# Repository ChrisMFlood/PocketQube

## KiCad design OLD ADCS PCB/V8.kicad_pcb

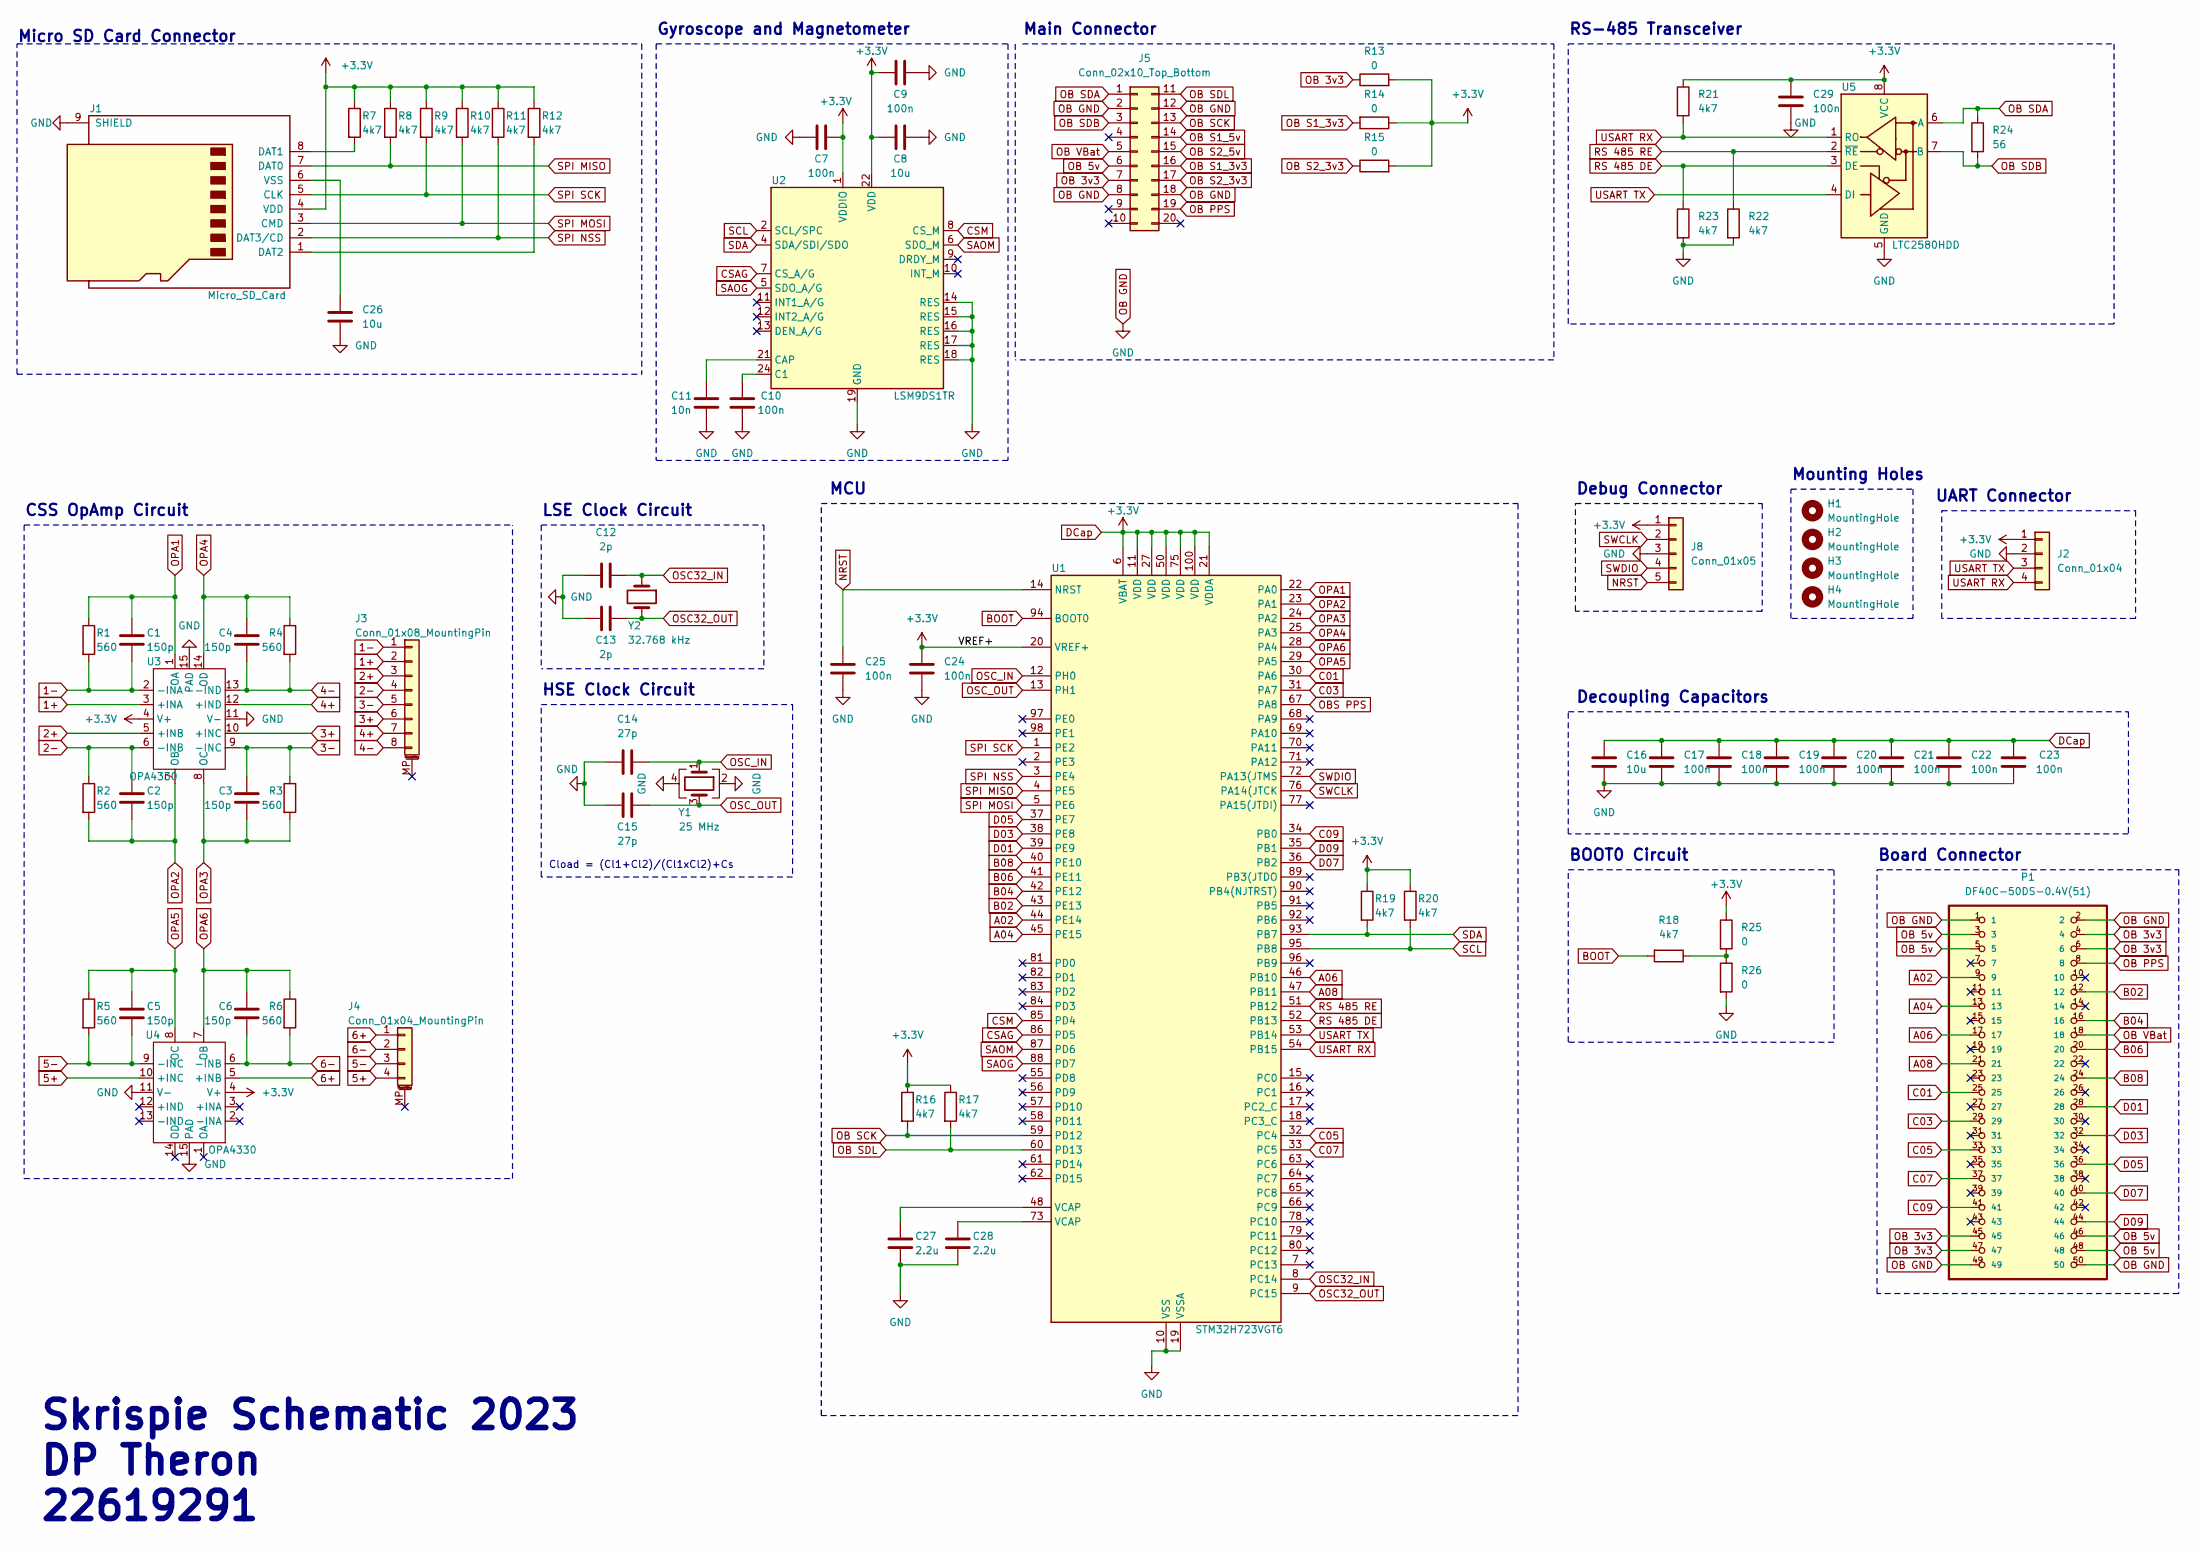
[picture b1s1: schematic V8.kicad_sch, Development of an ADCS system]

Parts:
C1, C2, C3, C4, C5, C6: 150p; C_0201_0603Metric
C7, C9, C10, C17, C18, C19, C20, C21, C22, C23, C24, C25, C29: 100n; C_0201_0603Metric
C8, C16, C26: 10u; C_0201_0603Metric
C11: 10n; C_0201_0603Metric
C12, C13: 2p; C_0201_0603Metric
C14, C15: 27p; C_0201_0603Metric
C27, C28: 2.2u; C_0201_0603Metric
H1, H2, H3, H4: MountingHole; MountingHole_2.5mm
J1: Micro_SD_Card; microSD_HC_Hirose_DM3AT-SF-PEJM5
J2: Conn_01x04; PinHeader_1x04_P1.27mm_Vertical
J3: Conn_01x08_MountingPin; JST_GH_SM08B-GHS-TB_1x08-1MP_P1.25mm_Horizontal
J4: Conn_01x04_MountingPin; JST_GH_SM04B-GHS-TB_1x04-1MP_P1.25mm_Horizontal
J5: Conn_02x10_Top_Bottom; SAMTEC-SMH-110-02-X-D_SMD
J8: Conn_01x05; PinHeader_1x05_P1.27mm_Vertical
P1: DF40C-50DS-0.4V(51); HRS_DF40C-50DS-0.4V(51)
R1, R2, R3, R4, R5, R6: 560; R_0201_0603Metric
R7, R8, R9, R10, R11, R12, R16, R17, R18, R19, R20, R21, R22, R23: 4k7; R_0201_0603Metric
R13, R14, R15, R25, R26: 0; R_0201_0603Metric
R24: 56; R_0201_0603Metric
U1: STM32H723VGT6; LQFP-100_14x14mm_P0.5mm
U2: LSM9DS1TR; LGA-24L_3x3.5mm_P0.43mm
U3, U4: OPA4330; Texas_S-PVQFN-N14
U5: LTC2580HDD; DFN-8-1EP_3x3mm_P0.5mm_EP1.65x2.38mm
Y1: 25 MHz; Crystal_SMD_EuroQuartz_X22-4Pin_2.5x2.0mm
Y2: 32.768 kHz; Crystal_SMD_EuroQuartz_EQ161-2Pin_3.2x1.5mm

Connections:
1+: J3.2, U3.3 (+INA)
1-: C1.2, J3.1, R1.2, U3.2 (-INA)
2+: J3.3, U3.5 (+INB)
2-: C2.1, J3.4, R2.1, U3.6 (-INB)
3+: J3.6, U3.10 (+INC)
3-: C3.1, J3.5, R3.1, U3.9 (-INC)
4+: J3.7, U3.12 (+IND)
4-: C4.2, J3.8, R4.2, U3.13 (-IND)
5+: J4.4, U4.10 (+INC)
5-: C5.2, J4.3, R5.2, U4.9 (-INC)
6+: J4.1, U4.5 (+INB)
6-: C6.2, J4.2, R6.2, U4.6 (-INB)
A02: P1.9, U1.44 (PE14)
A04: P1.13, U1.45 (PE15)
A06: P1.17, U1.46 (PB10)
A08: P1.21, U1.47 (PB11)
B02: P1.12, U1.43 (PE13)
B04: P1.16, U1.42 (PE12)
B06: P1.20, U1.41 (PE11)
B08: P1.24, U1.40 (PE10)
BOOT: R18.2, U1.94 (BOOT0)
C01: P1.25, U1.30 (PA6)
C03: P1.29, U1.31 (PA7)
C05: P1.33, U1.32 (PC4)
C07: P1.37, U1.33 (PC5)
C09: P1.41, U1.34 (PB0)
CSAG: U1.86 (PD5), U2.7 (CS_A/G)
CSM: U1.85 (PD4), U2.8 (CS_M)
D01: P1.28, U1.39 (PE9)
D03: P1.32, U1.38 (PE8)
D05: P1.36, U1.37 (PE7)
D07: P1.40, U1.36 (PB2)
D09: P1.44, U1.35 (PB1)
DCap: C7.2, C8.1, C9.1, C16.1, C17.1, C18.1, C19.1, C20.1, C21.1, C22.1, C23.1, C24.1, C29.1, J1.4 (VDD), J2.1, J8.1, R7.1, R8.1, R9.1, R10.1, R11.1, R12.1, R13.2, R14.1, R15.2, R16.1, R17.1, R19.1, R20.1, R21.1, R25.1, U1.6 (VBAT), U1.11 (VDD), U1.20 (VREF+), U1.21 (VDDA), U1.27 (VDD), U1.50 (VDD), U1.75 (VDD), U1.100 (VDD), U2.1 (VDDIO), U2.3 (VDDIO), U2.22 (VDD), U2.23 (VDD), U3.4 (V+), U4.4 (V+), U5.8 (VCC)
NRST: C25.1, J8.5, U1.14 (NRST)
unnamed: C27.1, U1.48 (VCAP)
unnamed: C28.1, U1.73 (VCAP)
unnamed: J1.8 (DAT1), R7.2
unnamed: J1.1 (DAT2), R12.2
unnamed: C26.1, J1.6 (VSS)
unnamed: R18.1, R25.2, R26.1
unnamed: C10.1, U2.24 (C1)
unnamed: C11.2, U2.21 (CAP)
OB 3v3: J5.7, P1.4, P1.6, P1.45, P1.47, R13.1
OB 5v: J5.6, P1.3, P1.5, P1.46, P1.48
OB GND: C7.1, C8.2, C9.2, C10.2, C11.1, C12.1, C13.1, C14.1, C15.1, C16.2, C17.2, C18.2, C19.2, C20.2, C21.2, C22.2, C23.2, C24.2, C25.2, C26.2, C27.2, C28.2, C29.2, J1.9 (SHIELD), J2.2, J5.2, J5.8, J5.12, J5.18, J8.3, P1.1, P1.2, P1.49, P1.50, R22.2, R23.2, R26.2, U1.10 (VSS), U1.19 (VSSA), U1.26 (VSS), U1.49 (VSS), U1.74 (VSS), U1.99 (VSS), U2.14 (RES), U2.15 (RES), U2.16 (RES), U2.17 (RES), U2.18 (RES), U2.19 (GND), U2.20 (GND), U3.11 (V-), U3.15 (PAD), U4.11 (V-), U4.15 (PAD), U5.5 (GND), U5.9 (GND), Y1.2, Y1.4
OB PPS: J5.19, P1.8
OB S1_3v3: J5.16, R14.2
OB S1_5v: J5.14
OB S2_3v3: J5.17, R15.1
OB S2_5v: J5.15
OB SCK: J5.13, R16.2, U1.59 (PD12)
OB SDA: J5.1, R24.1, U5.6 (A)
OB SDB: J5.3, R24.2, U5.7 (B)
OB SDL: J5.11, R17.2, U1.60 (PD13)
OB VBat: J5.5, P1.18
OBS PPS: U1.67 (PA8)
OPA1: C1.1, R1.1, U1.22 (PA0), U3.1 (OA)
OPA2: C2.2, R2.2, U1.23 (PA1), U3.7 (OB)
OPA3: C3.2, R3.2, U1.24 (PA2), U3.8 (OC)
OPA4: C4.1, R4.1, U1.25 (PA3), U3.14 (OD)
OPA5: C5.1, R5.1, U1.29 (PA5), U4.8 (OC)
OPA6: C6.1, R6.1, U1.28 (PA4), U4.7 (OB)
OSC32_IN: C12.2, U1.8 (PC14), Y2.1
OSC32_OUT: C13.2, U1.9 (PC15), Y2.2
OSC_IN: C14.2, U1.12 (PH0), Y1.1
OSC_OUT: C15.2, U1.13 (PH1), Y1.3
RS 485 DE: R23.1, U1.52 (PB13), U5.3 (DE)
RS 485 RE: R22.1, U1.51 (PB12), U5.2 (~RE)
SAOG: U1.88 (PD7), U2.5 (SDO_A/G)
SAOM: U1.87 (PD6), U2.6 (SDO_M)
SCL: R20.2, U1.95 (PB8), U2.2 (SCL/SPC)
SDA: R19.2, U1.93 (PB7), U2.4 (SDA/SDI/SDO)
SPI MISO: J1.7 (DAT0), R8.2, U1.4 (PE5)
SPI MOSI: J1.3 (CMD), R10.2, U1.5 (PE6)
SPI NSS: J1.2 (DAT3/CD), R11.2, U1.3 (PE4)
SPI SCK: J1.5 (CLK), R9.2, U1.1 (PE2)
SWCLK: J8.2, U1.76 (PA14(JTCK)
SWDIO: J8.4, U1.72 (PA13(JTMS)
USART RX: J2.4, R21.2, U1.54 (PB15), U5.1 (RO)
USART TX: J2.3, U1.53 (PB14), U5.4 (DI)

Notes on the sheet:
Gyroscope and Magnetometer
HSE Clock Circuit
Board Connector
Micro SD Card Connector
UART Connector
Skrispie Schematic 2023 DP Theron 22619291
Decoupling Capacitors
Mounting Holes
Cload = (Cl1+Cl2)/(Cl1xCl2)+Cs
CSS OpAmp Circuit
Debug Connector
LSE Clock Circuit
Main Connector
BOOT0 Circuit
MCU
RS-485 Transceiver

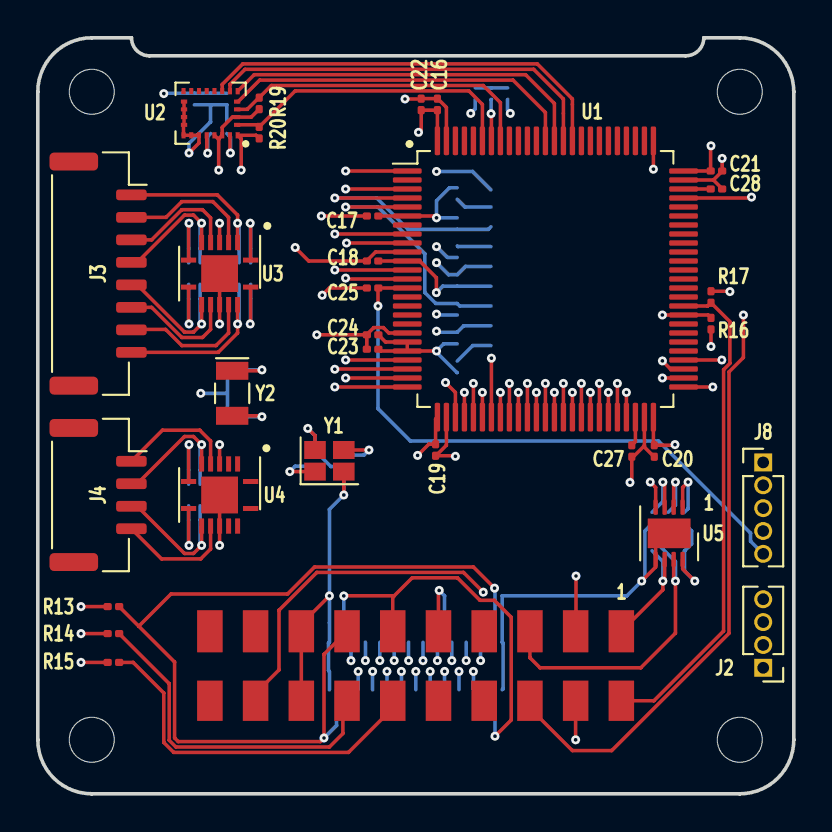
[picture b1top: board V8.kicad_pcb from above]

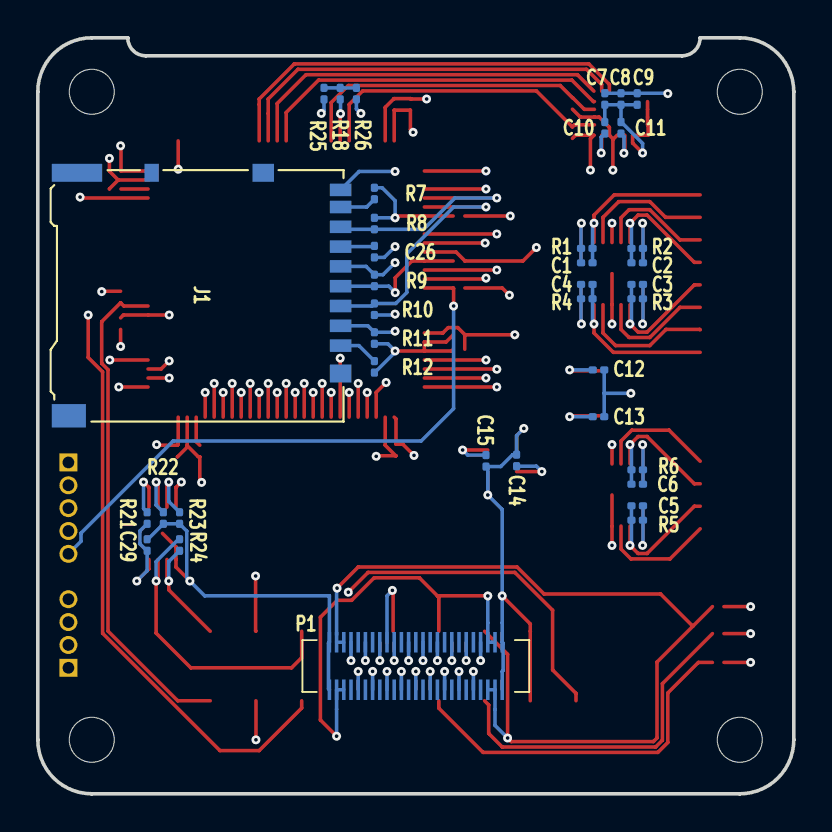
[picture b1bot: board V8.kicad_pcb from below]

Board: 4 copper layers, 42.0 x 42.0 mm, 73 parts (38 on the bottom side), 78 nets.

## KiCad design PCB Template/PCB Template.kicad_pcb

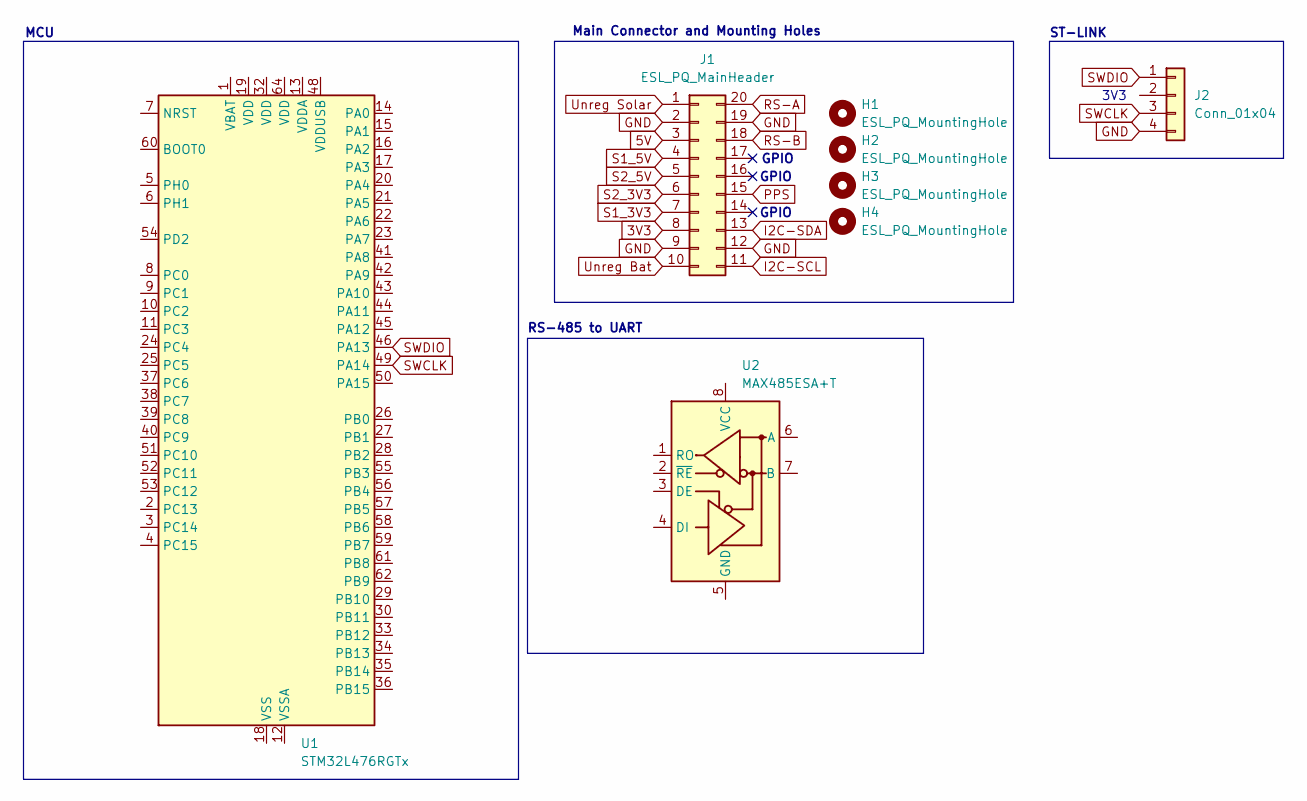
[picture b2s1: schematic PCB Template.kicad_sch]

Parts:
H1, H2, H3, H4: ESL_PQ_MountingHole
J1: ESL_PQ_MainHeader; ESL_PQ_Main_Header
J2: Conn_01x04; 1x04 1.27mm
U1: STM32L476RGTx; LQFP-64_10x10mm_P0.5mm; JLC Part# C74797
U2: MAX485ESA+T; SOIC-8_3.9x4.9mm_P1.27mm; JLC Part# C19738

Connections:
3V3: J1.8
5V: J1.3
GND: J1.2, J1.9, J1.12, J1.19, J2.4
GSU: J1.1
unnamed: U1.18 (VSS), U1.31 (VSS), U1.47 (VSS), U1.63 (VSS)
PPS: J1.15
S1_3V3: J1.7
S1_5V: J1.4
S2_3V3: J1.6
S2_5V: J1.5
SCK: J1.11
SDA: J1.20
SDB: J1.18
SDL: J1.13
SWCLK: J2.3, U1.49 (PA14)
SWDIO: J2.1, U1.46 (PA13)
VBat: J1.10

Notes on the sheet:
GPIO
MCU
ST-LINK
RS-485 to UART
3V3
Main Connector and Mounting Holes

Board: 2 copper layers, 8 parts (0 on the bottom side), 4 nets, no tracks yet.

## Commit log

2024-04-10 Initial
2024-04-10 Niel 1
2024-04-10 obc initial
